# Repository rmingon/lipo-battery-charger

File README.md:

# Lipo charger with mcp73831 and multiple charging speed

## this project use MCP73831 for charging lipo with multiple type of connectors.

### Charging speed selector
- 50ma use 20k resistor
- 100ma use 10k resistor
- 200ma use 5k resistor
- 500ma use 2k resistor
### You can change resistor with help of this grah (see datasheet for more info [HERE](https://ww1.microchip.com/downloads/en/DeviceDoc/MCP73831-Family-Data-Sheet-DS20001984H.pdf))

#### really easy calculator for charging speed to resistor to set
```javascript
const charging_speed = 500 // set here your charging speed desired in milliamps
if (charging_speed > 500) 
    alert("Can't charge more than 500ma")
else
    alert(1000/(charging_speed/1000)+"Ohm")
```

### 3d view

### Schematic screenshot

### Pcb screenshot

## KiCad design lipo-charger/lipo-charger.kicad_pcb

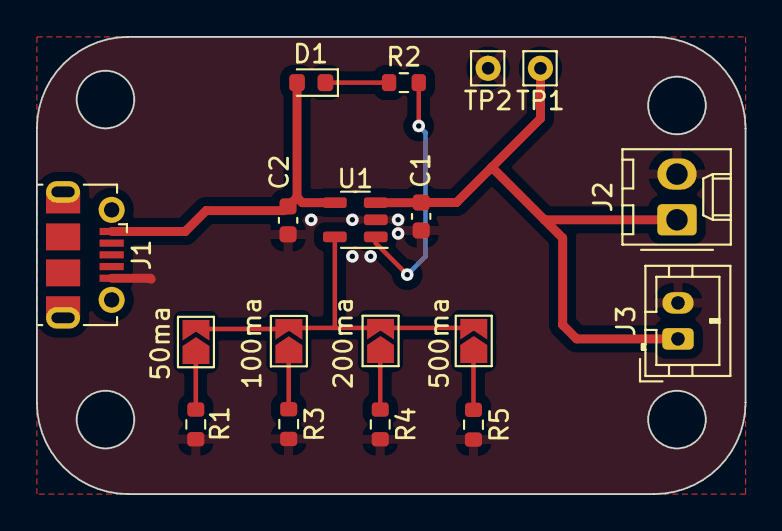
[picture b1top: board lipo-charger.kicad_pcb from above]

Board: 2 copper layers, 39.4 x 25.4 mm, 18 parts (0 on the bottom side), 10 nets.

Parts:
50ma, 100ma, 200ma, 500ma: Jumper_2_Open; SolderJumper-2_P1.3mm_Open_TrianglePad1.0x1.5mm
C1, C2: C_Small; C_0603_1608Metric
D1: LED; LED_0603_1608Metric
J1: USB_B_Micro; USB_Micro-B_Molex-105017-0001
J2: Screw_Terminal_01x02; Molex_KK-254_AE-6410-02A_1x02_P2.54mm_Vertical
J3: Conn_01x02; JST_PH_B2B-PH-K_1x02_P2.00mm_Vertical
R1, R2, R3, R4, R5: R_Small; R_0603_1608Metric
TP1, TP2: TestPoint; Pin_D0.7mm_L6.5mm_W1.8mm_FlatFork
U1: MCP73831-2-OT; SOT-23-5

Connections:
+5V: C2.1, D1.2 (A), J1.1 (VBUS), U1.4 (V_{DD})
GND: C1.2, C2.2, J1.5 (GND), J2.2, J3.2, R1.2, R3.2, R4.2, R5.2, TP2.1, U1.2 (V_{SS})
LIPO: C1.1, J2.1, J3.1, TP1.1, U1.3 (V_{BAT})
unnamed: D1.1 (K), R2.1
unnamed: 50ma.1 (A), R1.1
unnamed: 100ma.1 (A), R3.1
unnamed: 200ma.1 (A), R4.1
unnamed: 500ma.1 (A), R5.1
unnamed: R2.2, U1.1 (STAT)
PROG: 50ma.2 (B), 100ma.2 (B), 200ma.2 (B), 500ma.2 (B), U1.5 (PROG)

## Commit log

2023-07-26 add prog resistor
2023-07-26 mcp73 wired
2023-07-26 first pcb placed
2023-07-26 add connector
2023-07-26 update test + final wiring
2023-07-26 add screenshot
2023-07-26 add prog
2023-07-26 add readme
2023-07-26 up readme
